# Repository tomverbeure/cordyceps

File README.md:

# TDS3K Cordyceps

A Tektronix TDS3000(B) oscilloscope expansion board that fixes
the faulty Dallas DS1742W, adds a fast SCPI serial port, makes
the VxWorks console visible, enables all software options, and
more, without needing open the scope or install special firmware.

More information coming soon...

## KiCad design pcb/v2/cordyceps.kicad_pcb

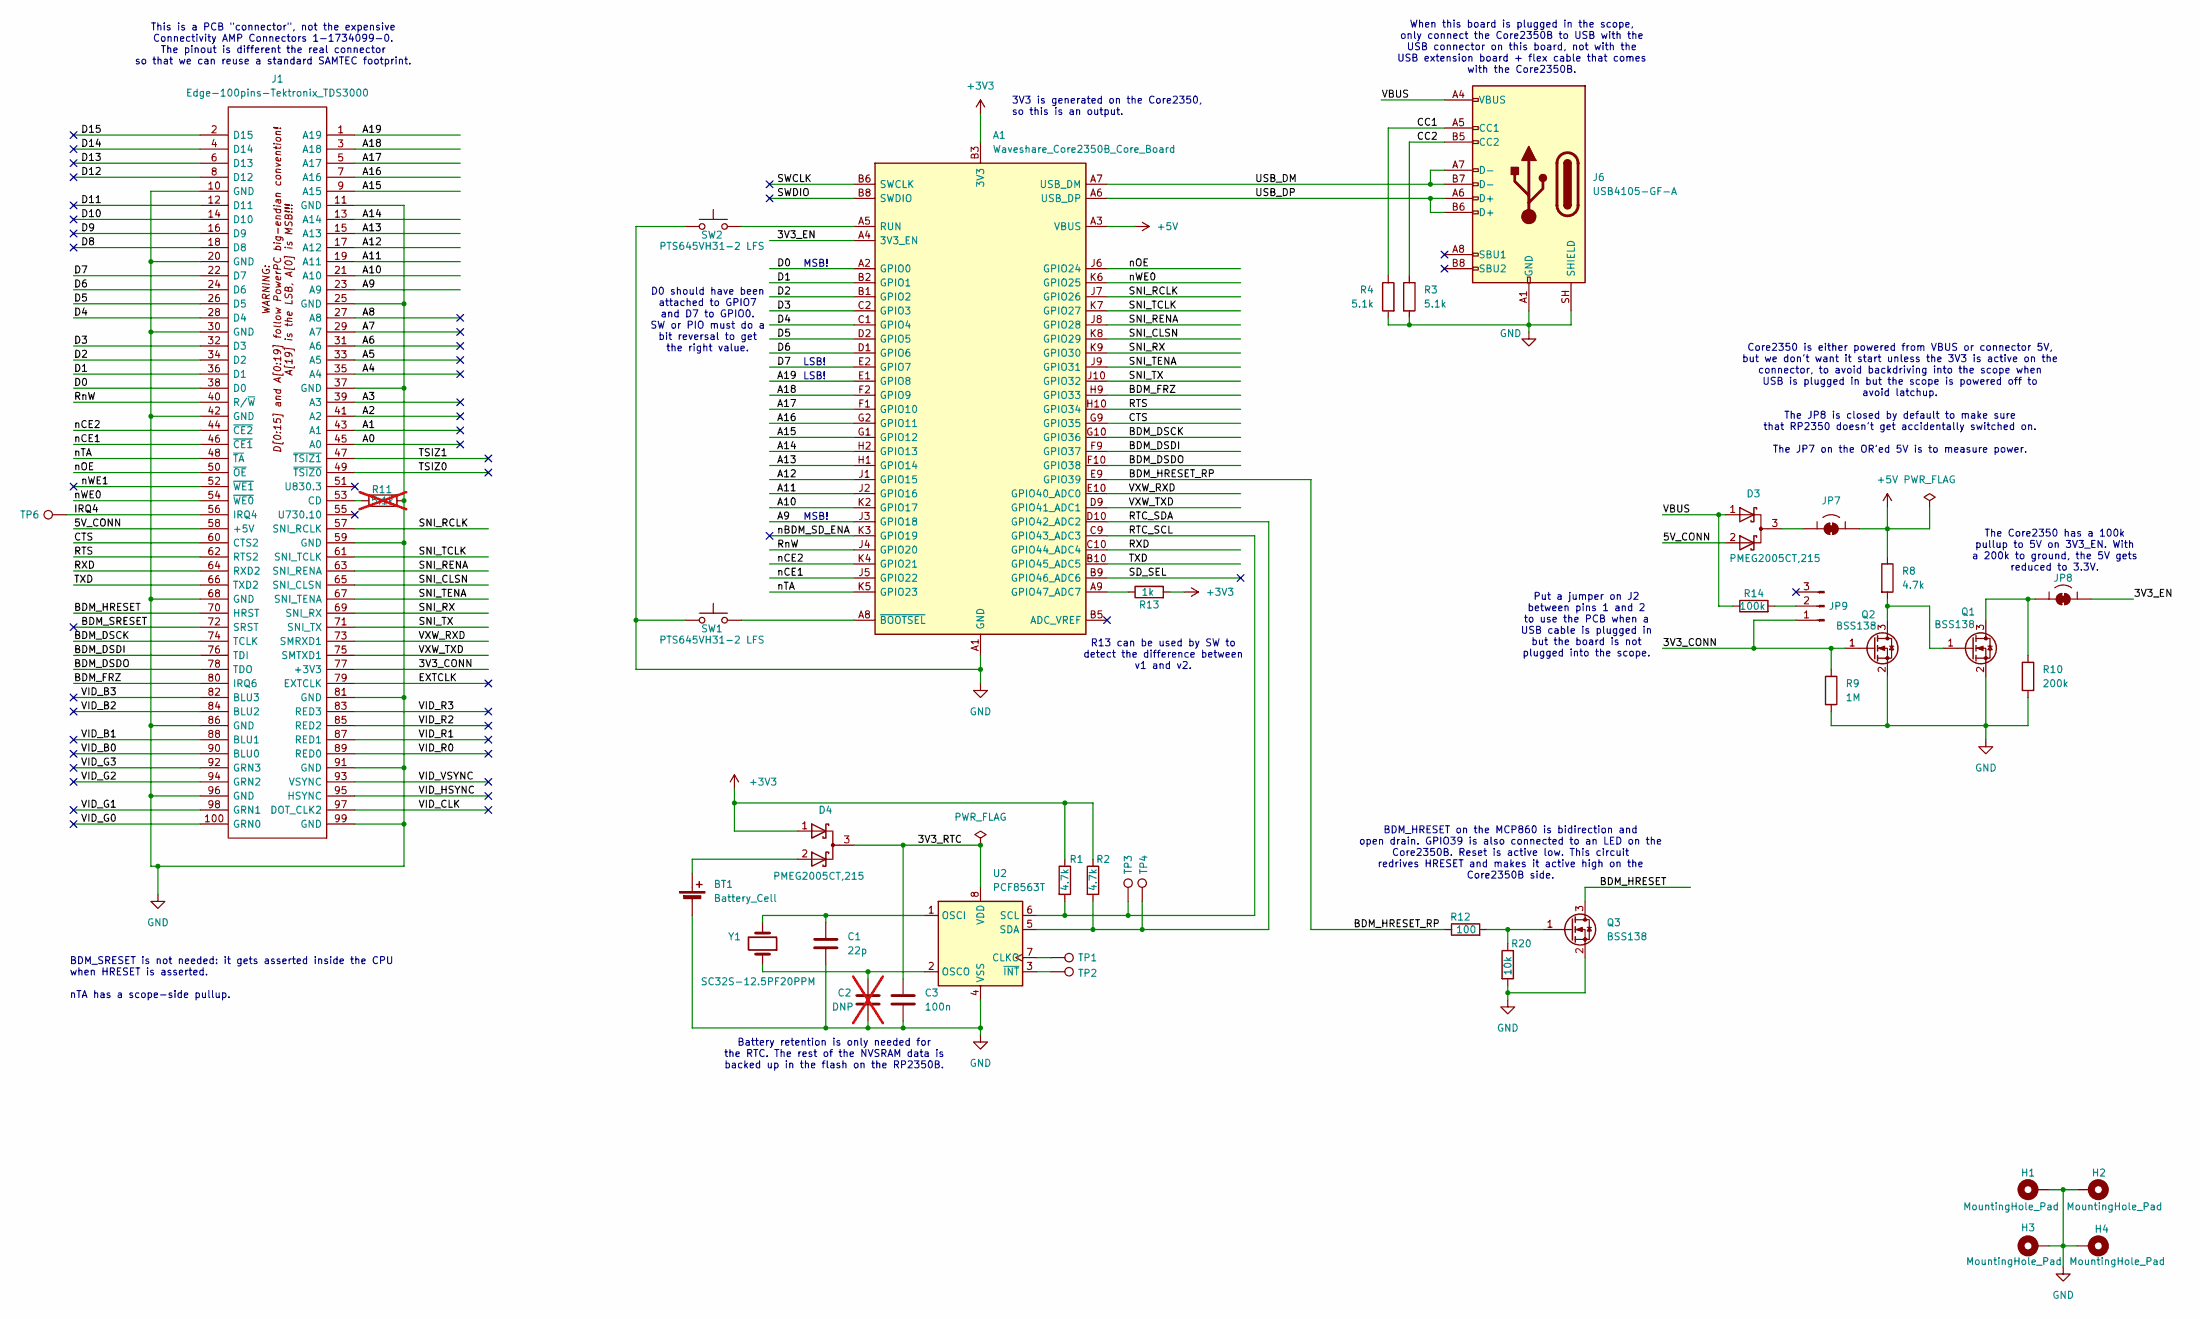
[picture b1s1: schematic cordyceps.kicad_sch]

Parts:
A1: Waveshare_Core2350B_Core_Board; Waveshare Core2350
BT1: Battery_Cell; BatteryHolder_Keystone_103_1x20mm
C1: 22p; C_0603_1608Metric
C2: DNP; C_0603_1608Metric; not fitted
C3: 100n; C_0603_1608Metric
D3, D4: PMEG2005CT,215; SOT-23-3
H1, H2, H3, H4: MountingHole_Pad; MountingHole_3.2mm_M3_Pad
J1: Edge-100pins-Tektronix_TDS3000; Samtec_MECF-50-0_-NP-L-DV_2x50_P1.27mm_Edge; Mouser Part Number 571-1-1734099-0
J6: USB4105-GF-A; USB_C_Receptacle_GCT_USB4105-xx-A_16P_TopMnt_Horizontal
JP7, JP8: SolderBridge_Jumper_2_Bridged
JP9: Conn_01x03_Pin; PinHeader_1x03_P2.54mm_Vertical
Q1, Q2, Q3: BSS138; SOT-23
R1, R2, R8: 4.7k; R_0603_1608Metric
R3, R4: 5.1k; R_0603_1608Metric
R9: 1M; R_0603_1608Metric
R10: 200k; R_0603_1608Metric
R11: 5.1k; R_0603_1608Metric; not fitted
R12: 100; R_0603_1608Metric
R13: 1k; R_0603_1608Metric
R14: 100k; R_0603_1608Metric
R20: 10k; R_0603_1608Metric
SW1, SW2: PTS645VH31-2 LFS; SW_Tactile_SPST_Angled_PTS645Vx31-2LFS
TP1, TP3, TP6: RTL_CLK0; TestPoint_THTPad_D1.0mm_Drill0.5mm
TP2, TP4: RTC_nINT; TestPoint_THTPad_D1.0mm_Drill0.5mm
U2: PCF8563T; SOIC-8_3.9x4.9mm_P1.27mm
Y1: SC32S-12.5PF20PPM; Crystal_SMD_3215-2Pin_3.2x1.5mm

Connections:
+3V3: A1.B3 (3V3), D4.1 (A), R1.1, R2.1, R13.2
+5V: A1.A3 (VBUS), JP7.2 (B), R8.1
/3V3_CONN: J1.77 (+3V3), JP9.1, Q2.1 (G), R9.1
/3V3_EN: A1.A4 (3V3_EN), JP8.2 (B)
/3V3_RTC: C3.1, D4.3 (K), U2.8 (VDD)
/5V_CONN: D3.2 (A), J1.58 (+5V)
/A0: J1.45 (A0)
/A1: J1.43 (A1)
/A2: J1.41 (A2)
/A3: J1.39 (A3)
/A4: J1.35 (A4)
/A5: J1.33 (A5)
/A6: J1.31 (A6)
/A7: J1.29 (A7)
/A8: J1.27 (A8)
/A9: A1.J3 (GPIO18), J1.23 (A9)
/A10: A1.K2 (GPIO17), J1.21 (A10)
/A11: A1.J2 (GPIO16), J1.19 (A11)
/A12: A1.J1 (GPIO15), J1.17 (A12)
/A13: A1.H1 (GPIO14), J1.15 (A13)
/A14: A1.H2 (GPIO13), J1.13 (A14)
/A15: A1.G1 (GPIO12), J1.9 (A15)
/A16: A1.G2 (GPIO11), J1.7 (A16)
/A17: A1.F1 (GPIO10), J1.5 (A17)
/A18: A1.F2 (GPIO9), J1.3 (A18)
/A19: A1.E1 (GPIO8), J1.1 (A19)
/BDM_DSCK: A1.G10 (GPIO36), J1.74 (TCLK)
/BDM_DSDI: A1.F9 (GPIO37), J1.76 (TDI)
/BDM_DSDO: A1.F10 (GPIO38), J1.78 (TDO)
/BDM_FRZ: A1.H9 (GPIO33), J1.80 (IRQ6)
/BDM_HRESET: J1.70 (HRST), Q3.3 (D)
/BDM_HRESET_RP: A1.E9 (GPIO39), R12.1
/BDM_SRESET: J1.72 (SRST)
/CC1: J6.A5 (CC1), R4.1
/CC2: J6.B5 (CC2), R3.1
/CTS: A1.G9 (GPIO35), J1.60 (CTS2)
/D0: A1.A2 (GPIO0), J1.38 (D0)
/D1: A1.B2 (GPIO1), J1.36 (D1)
/D2: A1.B1 (GPIO2), J1.34 (D2)
/D3: A1.C2 (GPIO3), J1.32 (D3)
/D4: A1.C1 (GPIO4), J1.28 (D4)
/D5: A1.D2 (GPIO5), J1.26 (D5)
/D6: A1.D1 (GPIO6), J1.24 (D6)
/D7: A1.E2 (GPIO7), J1.22 (D7)
/D8: J1.18 (D8)
/D9: J1.16 (D9)
/D10: J1.14 (D10)
/D11: J1.12 (D11)
/D12: J1.8 (D12)
/D13: J1.6 (D13)
/D14: J1.4 (D14)
/D15: J1.2 (D15)
/EXTCLK: J1.79 (EXTCLK)
/IRQ4: J1.56 (IRQ4), TP6.1 (1_1)
/RTC_SCL: A1.C9 (GPIO43_ADC3), R1.2, TP3.1 (1_1), U2.6 (SCL)
/RTC_SDA: A1.D10 (GPIO42_ADC2), R2.2, TP4.1 (1_1), U2.5 (SDA)
/RTS: A1.H10 (GPIO34), J1.62 (RTS2)
/RXD: A1.C10 (GPIO44_ADC4), J1.64 (RXD2)
/RnW: A1.J4 (GPIO20), J1.40 (R/~W)
/SD_SEL: A1.B9 (GPIO46_ADC6)
/SNI_CLSN: A1.K8 (GPIO29), J1.65 (SNI_CLSN)
/SNI_RCLK: A1.J7 (GPIO26), J1.57 (SNI_RCLK)
/SNI_RENA: A1.J8 (GPIO28), J1.63 (SNI_RENA)
/SNI_RX: A1.K9 (GPIO30), J1.69 (SNI_RX)
/SNI_TCLK: A1.K7 (GPIO27), J1.61 (SNI_TCLK)
/SNI_TENA: A1.J9 (GPIO31), J1.67 (SNI_TENA)
/SNI_TX: A1.J10 (GPIO32), J1.71 (SNI_TX)
/SWCLK: A1.B6 (SWCLK)
/SWDIO: A1.B8 (SWDIO)
/TSIZ0: J1.49 (~TSIZ0)
/TSIZ1: J1.47 (~TSIZ1)
/TXD: A1.B10 (GPIO45_ADC5), J1.66 (TXD2)
/USB_DM: A1.A7 (USB_DM), J6.A7 (D-), J6.B7 (D-)
/USB_DP: A1.A6 (USB_DP), J6.A6 (D+), J6.B6 (D+)
/VBUS: D3.1 (A), J6.A4 (VBUS), J6.A9 (VBUS), J6.B4 (VBUS), J6.B9 (VBUS), R14.1
/VID_B0: J1.90 (BLU0)
/VID_B1: J1.88 (BLU1)
/VID_B2: J1.84 (BLU2)
/VID_B3: J1.82 (BLU3)
/VID_CLK: J1.97 (DOT_CLK2)
/VID_G0: J1.100 (GRN0)
/VID_G1: J1.98 (GRN1)
/VID_G2: J1.94 (GRN2)
/VID_G3: J1.92 (GRN3)
/VID_HSYNC: J1.95 (HSYNC)
/VID_R0: J1.89 (RED0)
/VID_R1: J1.87 (RED1)
/VID_R2: J1.85 (RED2)
/VID_R3: J1.83 (RED3)
/VID_VSYNC: J1.93 (VSYNC)
/VXW_RXD: A1.E10 (GPIO40_ADC0), J1.73 (SMRXD1)
/VXW_TXD: A1.D9 (GPIO41_ADC1), J1.75 (SMTXD1)
/nBDM_SD_ENA: A1.K3 (GPIO19)
/nCE1: A1.J5 (GPIO22), J1.46 (~CE1)
/nCE2: A1.K4 (GPIO21), J1.44 (~CE2)
/nOE: A1.J6 (GPIO24), J1.50 (~OE)
/nTA: A1.K5 (GPIO23), J1.48 (~TA)
/nWE0: A1.K6 (GPIO25), J1.54 (~WE0)
/nWE1: J1.52 (~WE1)
GND: A1.A1 (GND), A1.A10 (GND), A1.B4 (GND), A1.B7 (GND), A1.K1 (GND), A1.K10 (GND), BT1.2 (-), C1.2, C2.2, C3.2, H1.1 (1_1), H2.1 (1_1), H3.1 (1_1), H4.1 (1_1), J1.10 (GND), J1.11 (GND), J1.20 (GND), J1.25 (GND), J1.30 (GND), J1.37 (GND), J1.42 (GND), J1.59 (GND), J1.68 (GND), J1.81 (GND), J1.86 (GND), J1.91 (GND), J1.96 (GND), J1.99 (GND), J6.A1 (GND), J6.A12 (GND), J6.B1 (GND), J6.B12 (GND), J6.SH (SHIELD), Q1.2 (S), Q2.2 (S), Q3.2 (S), R3.2, R4.2, R9.2, R10.2, R11.2, R20.2, SW1.2, SW2.2, U2.4 (VSS)
unnamed: A1.A9 (GPIO47_ADC7), R13.1
unnamed: A1.A5 (RUN), SW2.1
unnamed: A1.A8 (~BOOTSEL), SW1.1
unnamed: BT1.1 (+), D4.2 (A)
unnamed: D3.3 (K), JP7.1 (A)
unnamed: J1.53 (CD), R11.1
unnamed: JP8.1 (A), Q1.3 (D), R10.1
unnamed: JP9.2, R14.2
unnamed: Q1.1 (G), Q2.3 (D), R8.2
unnamed: Q3.1 (G), R12.2, R20.1
unnamed: TP1.1 (1_1), U2.7 (CLKO)
unnamed: C1.1, U2.1 (OSCI), Y1.2
unnamed: C2.1, U2.2 (OSCO), Y1.1
unnamed: TP2.1 (1_1), U2.3 (~INT)

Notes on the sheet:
Battery retention is only needed for the RTC. The rest of the NVSRAM data is backed up in the flash on the RP2350B.
LSB!
When this board is plugged in the scope, only connect the Core2350B to USB with the USB connector on this board, not with the USB extension board + flex cable that comes with the Core2350B.
D0 should have been attached to GPIO7 and D7 to GPIO0. SW or PIO must do a bit reversal to get the right value.
Core2350 is either powered from VBUS or connector 5V, but we don't want it start unless the 3V3 is active on the connector, to avoid backdriving into the scope when USB is plugged in but the scope is powered off to avoid latchup. The JP8 is closed by default to make sure that RP2350 doesn't get acc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
3V3 is generated on the Core2350, so this is an output.
MSB!
Put a jumper on J2 between pins 1 and 2 to use the PCB when a USB cable is plugged in but the board is not plugged into the scope.
The Core2350 has a 100k pullup to 5V on 3V3_EN. With a 200k to ground, the 5V gets reduced to 3.3V.
BDM_HRESET on the MCP860 is bidirection and open drain. GPIO39 is also connected to an LED on the Core2350B. Reset is active low. This circuit redrives HRESET and makes it active high on the Core2350B side.
R13 can be used by SW to detect the difference between v1 and v2.
BDM_SRESET is not needed: it gets asserted inside the CPU when HRESET is asserted. nTA has a scope-side pullup.
This is a PCB "connector", not the expensive Connectivity AMP Connectors 1-1734099-0. The pinout is different the real connector so that we can reuse a standard SAMTEC footprint.

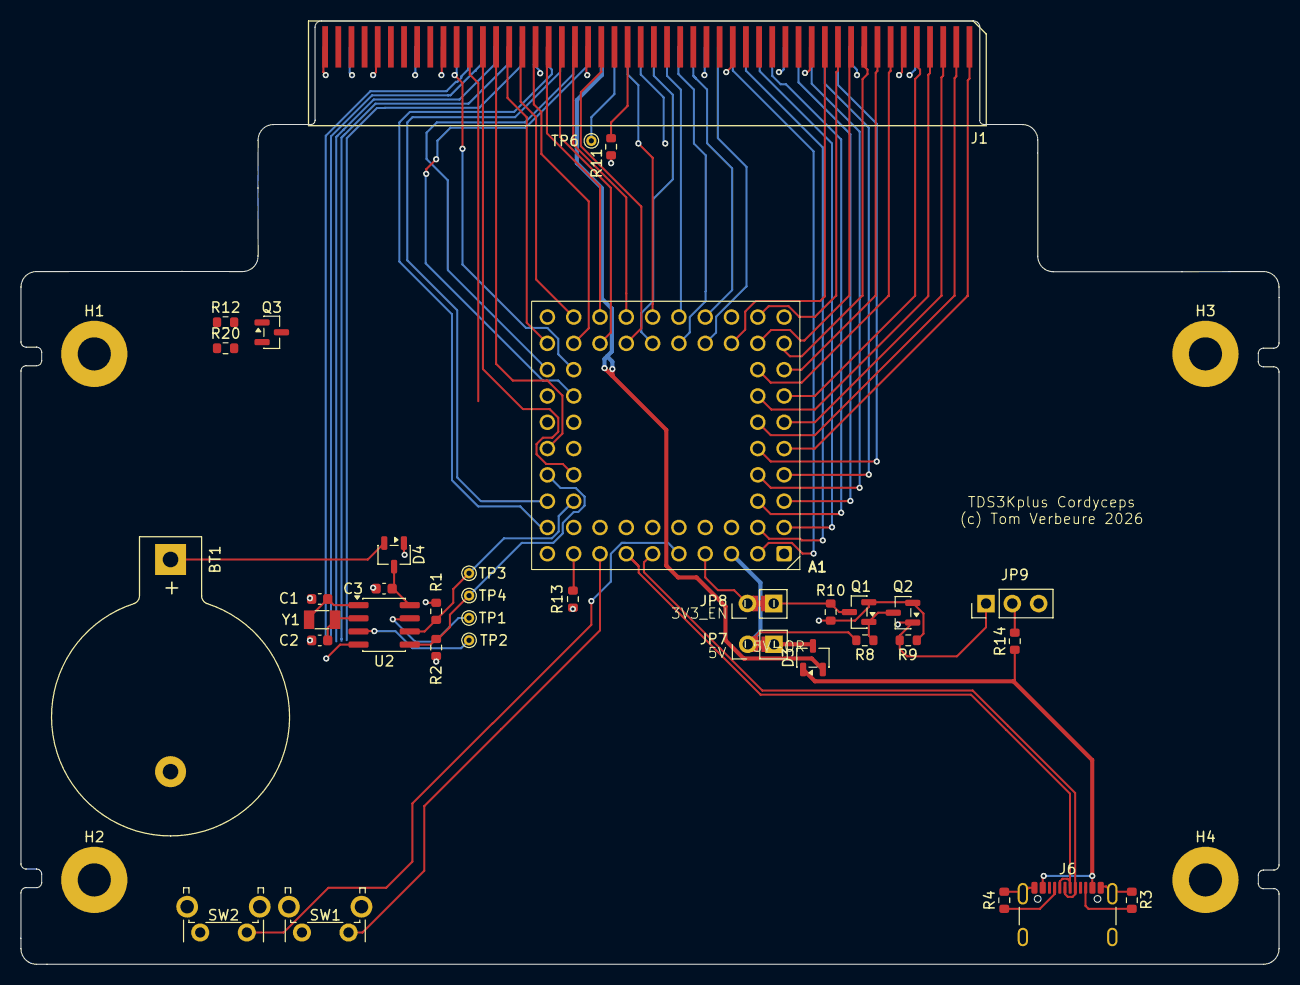
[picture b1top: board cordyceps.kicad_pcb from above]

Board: 4 copper layers, 121.5 x 91.1 mm, 40 parts (0 on the bottom side), 73 nets.

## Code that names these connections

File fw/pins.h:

#ifndef CORDYCEPS_PINS_H
#define CORDYCEPS_PINS_H

//============================================================
// MPC860 CPU bus
//============================================================
// D0 is the most significant bit of the MPC860 byte lane.
#define D0              0
#define D1              1
#define D2              2
#define D3              3
#define D4              4
#define D5              5
#define D6              6
#define D7              7

// A19 is the LSB!!!
#define A19             8
#define A18             9
#define A17            10
#define A16            11
#define A15            12
#define A14            13
#define A13            14
#define A12            15
#define A11            16
#define A10            17
#define A9             18

#define RnW            20
#define nCE2           21
#define nCE1           22
#define nTA            23
#define nOE            24
#define nWE            25

// Enable the bidir multiplexers that select between the BDM and SDcard interface
#define nBDM_SD_ENA    19
// Select SDcard instead of BDM on multiplexer
#define SD_SEL         46

// Serial Ethernet MAC interface
#define SNI_RCLK       26
#define SNI_TCLK       27
#define SNI_RENA       28
#define SNI_CLSN       29
#define SNI_RX         30
#define SNI_TENA       31
#define SNI_TX         32

// BDM signals - also used for SDcard (except HRESET)
#define BDM_HRESET     39
#define BDM_FRZ        33
#define BDM_DSCK       36
#define BDM_DSDI       37
#define BDM_DSDO       38

// VxWorks console UART - always 38400 baud - mapped to RP2350B UART1
#define VXW_RXD        40       // Connected to Pico UART TXD
#define VXW_TXD        41       // Connected to Pico UART RXD

// SCPI UART - mapped to RP2350B UART1 - mapped to RP2350 UART0
#define RXD            44       // Connected to Pico UART TXD
#define TXD            45       // Connected to Pico UART RXD
#define RTS            34       // Connected to Pico UART CTS
#define CTS            35       // Connected to Pico UART RTS

// PCF8563T Real-Time Clock I2C
#define RTC_SDA        42
#define RTC_SCL        43

#endif
